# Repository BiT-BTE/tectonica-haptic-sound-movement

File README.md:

##

Tectonica by BiT is a research project funded by the European Research Council (ERC) and led by Prof. Ana Tajadura-Jiménez. The project will run from January 2022 to December 2026 within the Department of Computer Science at Universidad Carlos III de Madrid, Spain.

# Objective
The main objective of Tectonica by BODYinTRANSIT is to share our advances in haptic prototypes develoment related with Body Transformation Experience (BTE).

# Prototypes
Our prototypes deliver sensory feedback, such as sound, vibrations, mechanical touch, etc. Among them is Tectótica, a series of prototypes dedicated to creating haptic sensory stimulation through various types of actuators.

# Publications
Here you can find publications related to the project: 
- [Exploring the Design Space for Body Transformation Wearables to Support Physical Activity through Sensitizing and Bodystorming](https://dl.acm.org/doi/abs/10.1145/3537972.3538001)

# How to contribute
If you are interested in collaborating with the project, please visit our  for more information [Link](https://bodyintransit.eu/participate-imbodylab/).

# Contact
For any questions or comments, please contact us at bodyintransit[at]uc3m.es.

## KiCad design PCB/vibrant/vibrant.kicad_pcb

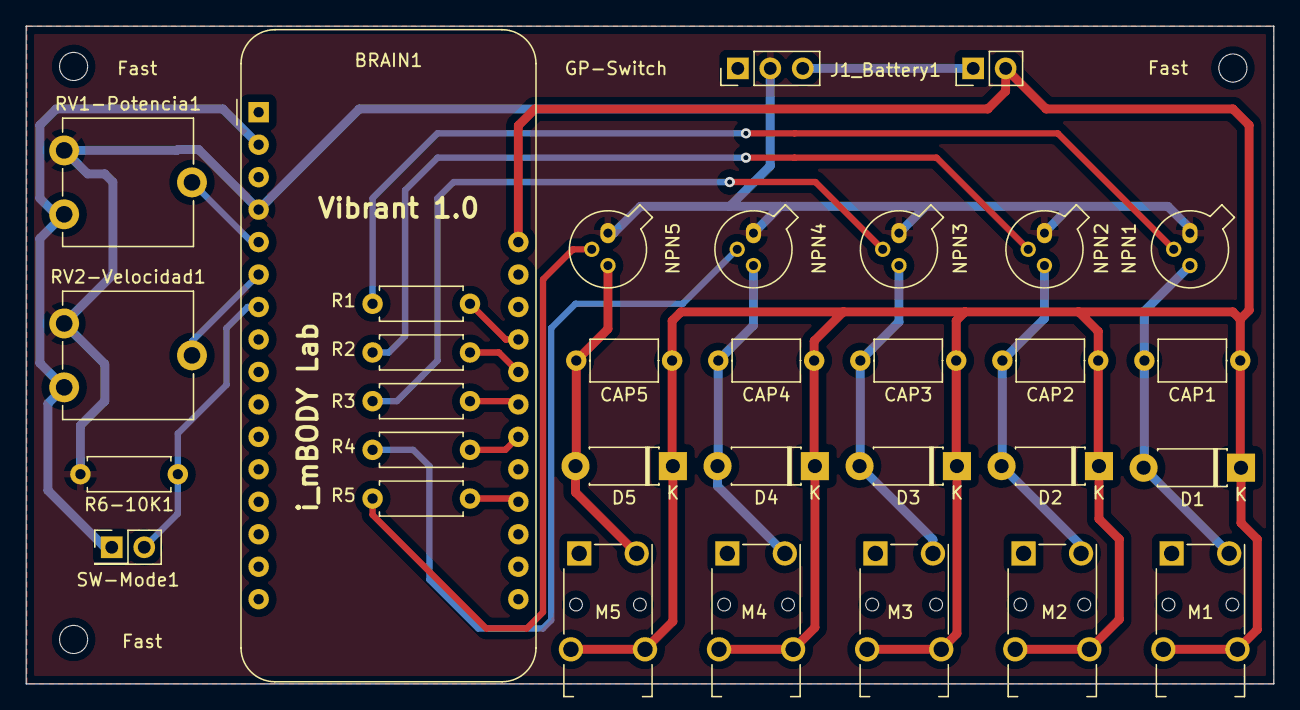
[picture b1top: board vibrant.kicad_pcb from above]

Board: 2 copper layers, 97.6 x 51.5 mm, 35 parts (0 on the bottom side), 22 nets.

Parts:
BRAIN1: Adafruit_Feather_HUZZAH32_ESP32; Adafruit_Feather
CAP1, CAP2, CAP3, CAP4, CAP5: C; C_Axial_L5.1mm_D3.1mm_P7.50mm_Horizontal
D1, D2, D3, D4, D5: 1N4007; D_DO-41_SOD81_P7.62mm_Horizontal
Fast: MountingHole_2.2mm_M2_DIN965
Fast#2, Fast#3: MountingHole_2.2mm_M2_DIN965
GP-Switch: SW_SPDT; PinHeader_1x03_P2.54mm_Vertical
J1_Battery1: Conn_01x02; PinHeader_1x02_P2.54mm_Vertical
M1, M2, M3, M4, M5: Motor DC; Jack_3.5mm_Switronic_ST-005-G_horizontal
NPN1, NPN2, NPN3, NPN4, NPN5: 2N2219; TO-18-3
R1, R2, R3, R4, R5, R6-10K1: R; R_Axial_DIN0207_L6.3mm_D2.5mm_P7.62mm_Horizontal
RV1-Potencia1, RV2-Velocidad1: R_Potentiometer; Potentiometer_ACP_CA9-V10_Vertical
SW-Mode1: SW_Push; PinHeader_2x01_P2.54mm_Vertical

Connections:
+3.3VP: BRAIN1.28 (VBAT), CAP1.1, CAP2.1, CAP3.1, CAP4.1, CAP5.1, D1.1 (K), D2.1 (K), D3.1 (K), D4.1 (K), D5.1 (K), J1_Battery1.2, M1.T, M2.T, M3.T, M4.T, M5.T
GND: BRAIN1.4 (GND), GP-Switch.2 (B), NPN1.1 (E), NPN2.1 (E), NPN3.1 (E), NPN4.1 (E), NPN5.1 (E), R6-10K1.2, RV1-Potencia1.3, RV2-Velocidad1.3
unnamed: BRAIN1.2 (3V3), RV1-Potencia1.1, RV2-Velocidad1.1, SW-Mode1.1
unnamed: BRAIN1.5 (DAC2/A0), RV1-Potencia1.2
unnamed: BRAIN1.6 (DAC1/A1), RV2-Velocidad1.2
unnamed: BRAIN1.7 (I34/A2), R6-10K1.1, SW-Mode1.2
unnamed: BRAIN1.20 (A7/IO32), R5.1
unnamed: BRAIN1.22 (A9/IO33), R4.1
unnamed: BRAIN1.23 (A10/IO27), R3.1
unnamed: BRAIN1.24 (A11/IO12), R2.1
unnamed: BRAIN1.25 (A12/IO13), R1.1
unnamed: CAP1.2, D1.2 (A), M1.S, NPN1.3 (C)
unnamed: CAP2.2, D2.2 (A), M2.S, NPN2.3 (C)
unnamed: CAP3.2, D3.2 (A), M3.S, NPN3.3 (C)
unnamed: CAP4.2, D4.2 (A), M4.S, NPN4.3 (C)
unnamed: CAP5.2, D5.2 (A), M5.S, NPN5.3 (C)
unnamed: NPN1.2 (B), R1.2
unnamed: NPN2.2 (B), R2.2
unnamed: NPN3.2 (B), R3.2
unnamed: NPN4.2 (B), R4.2
unnamed: NPN5.2 (B), R5.2
unnamed: GP-Switch.3 (C), J1_Battery1.1

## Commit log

2023-07-05 Primer Subida
    Paso del repo de Joaku al del Lab
2023-07-05 limpieza
2023-07-05 Suxin
2023-07-05 variacion
2023-07-05 sixin
2023-07-05 problema de descarga
2023-07-05 adios ableton
2023-07-05 ciao
2023-07-05 Last update
2023-07-05 adios
2023-07-05 Para sejo
2023-07-05 Vibrant1 Ready
2023-07-11 Inizialized
2023-07-11 cleaning
2023-10-13 Tectonica
2025-02-20 gitignore added
